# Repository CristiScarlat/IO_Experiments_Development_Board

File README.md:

IO_Experiments is a developer kit on a single board. The developer can connect any uC board including Arduino , Nucleo , RasperryPi to any of the devices on this board.

The board contains:
1. LCD 16x2 alphanumeric;
2. 8xleds driven by ULN2803;
3. 8xpush buttons;
4. 8xPots;
5. 7 segment display driven with cd4511;
6. 1x led matrix display driven by a MAX7219
7. 1xConnection made for Aurel 433MHz transiver;
8. 1xRTC PCF8563 I2C;
9. 3xIO Expanders MCP23017 I2C;
10. 1xEEPROM AT24CP I2C;
11. 1xFLASH MEM 25VF512A SPI ;
12. 1xDC Motor Drive L298;
13. 8xToggle Switches;
14. 1xRotary Encoder;
15. 1xJoystick;
16. 1xPiezzo Buzzer;
17. 1xLight Sensor;
18. 1xTemperature Sensor TMP36;
19 1xIR sensor 38KHz TSOP3483;
10. 1xDAC 12bit MCP4921 SPI ;
11. 1xADC 12bit MCP3201 SPI;
12. 8xRelays driven by ULN2803;

The boards has a 5V 3A power regulator and 3.3V 800mA power regulator.

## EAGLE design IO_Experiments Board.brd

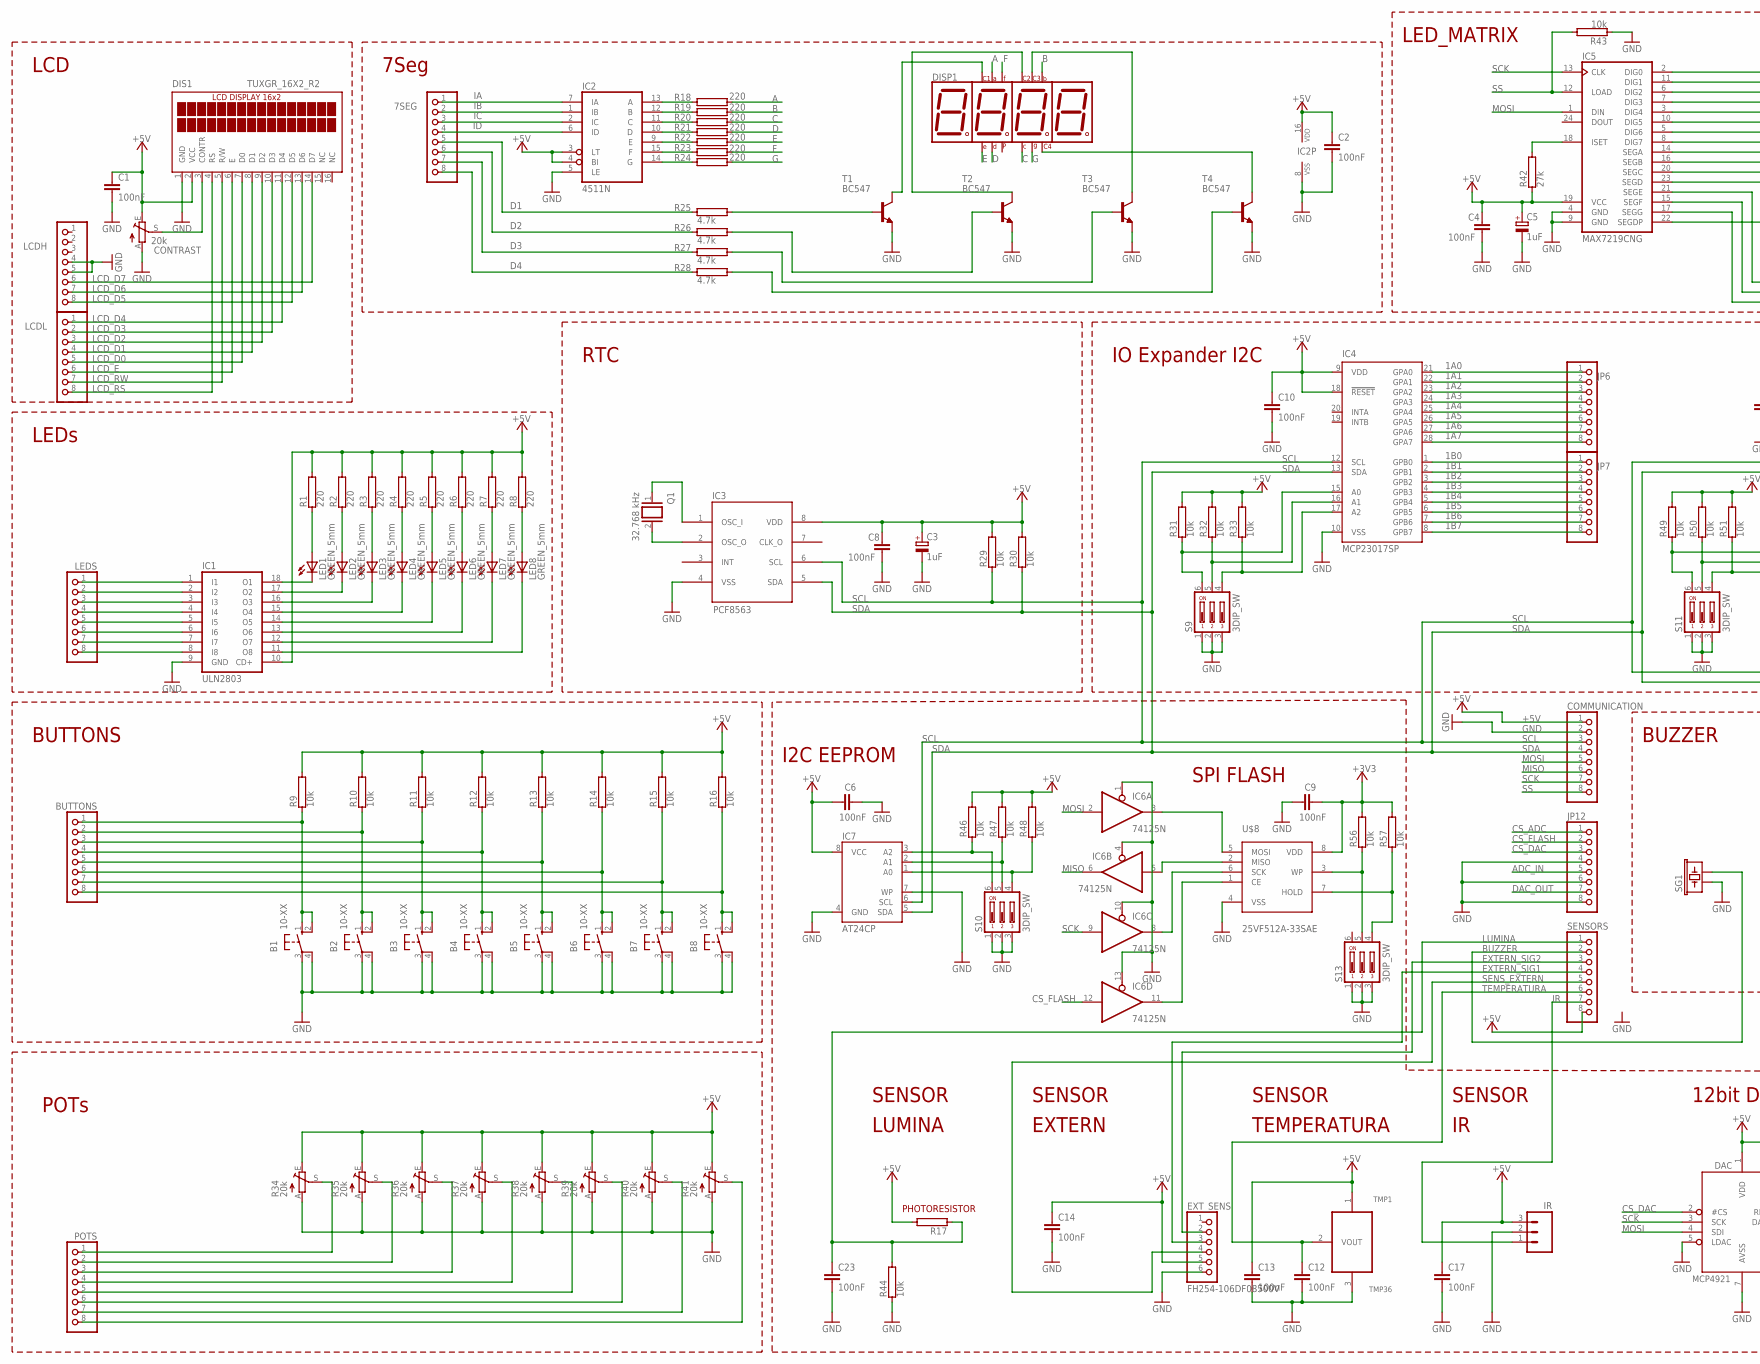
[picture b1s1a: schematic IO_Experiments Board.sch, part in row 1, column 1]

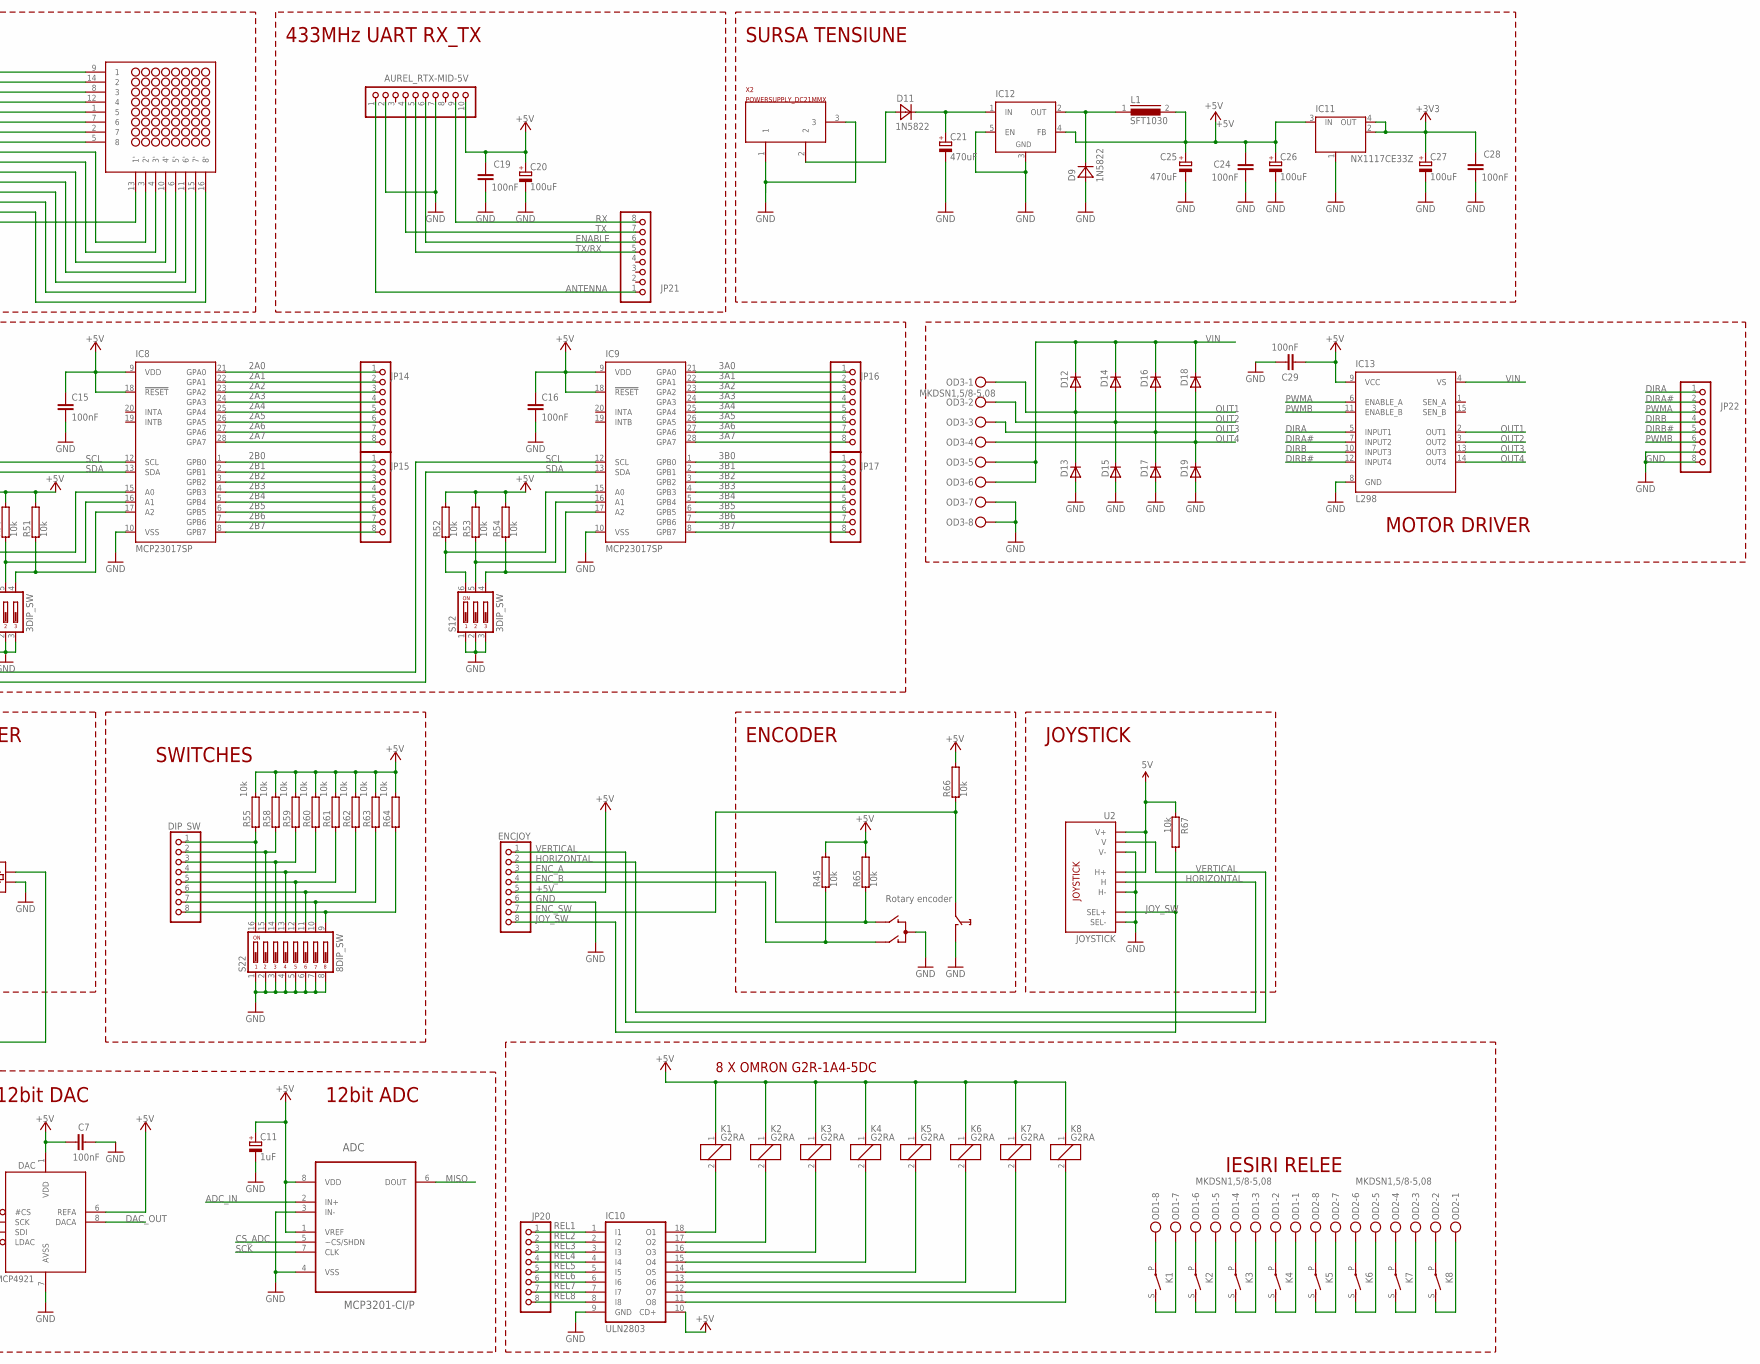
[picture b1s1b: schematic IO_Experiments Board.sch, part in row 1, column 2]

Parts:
7SEG: FH254-108DF08500V; 1X08
ADC: MCP3201-CI/P; DIL08
AUREL_RTX-MID-5V: FH254-110DF08500V; 1X10
B1, B2, B3, B4, B5, B6, B7, B8: 10-XX; B3F-10XX
BUTTONS: FH254-108DF08500V; 1X08
C1, C2, C4, C6, C7, C8, C9, C10, C12, C13, C14, C15, C16, C17, C19, C23, C24, C28, C29: 100nF; C5B2.5
C3, C5: 1uF; E2,5-6
C11: 1uF; E2,5-5
C20, C26, C27: 100uF; E2,5-6
C21, C25: 470uF; E5-10,5
COMMUNICATION: FH254-108DF08500V; 1X08
CONTRAST: 20k; CA6V
D9, D11: 1N5822; DO201-15
D12, D13, D14, D15, D16, D17, D18, D19: MBRA140; DO201-15
DAC: MCP4921; DIL08
DIP_SW: FH254-108DF08500V; 1X08
DIS1: TUXGR_16X2_R2
DISP1: LFD039AUE
ENCJOY: FH254-108DF08500V; 1X08
EXT_SENS: FH254-106DF08500V; 1X06
IC1, IC10: ULN2803; DIL18
IC2: 4511N; DIL16
IC3: PCF8563P; DIL08
IC4, IC8, IC9: MCP23017SP; DIL28-3
IC5: MAX7219CNG; DIL24-3
IC6: 74125N; DIL14
IC7: AT24CP; DIL08
IC11: NX1117CE33Z; SOT223
IC12: LM2596TV; TO220-51
IC13: L298; MULTIWATT-15
IR: M03LONGPADS; 1X03_LONGPADS
JP6, JP7, JP12, JP14, JP15, JP16, JP17, JP20, JP21, JP22: FH254-108DF08500V; 1X08
K1, K2, K3, K4, K5, K6, K7, K8: G2RA
L1: SFT1030
LCDH: FH254-108DF08500V; 1X08
LCDL: FH254-108DF08500V; 1X08
LED1, LED2, LED3, LED4, LED5, LED6, LED7, LED8: GREEN_5mm; LED5MM
LEDS: FH254-108DF08500V; 1X08
OD1, OD2, OD3: MKDSN1,5/8-5,08
POTS: FH254-108DF08500V; 1X08
Q1: 32.768 kHz; QS
R1, R2, R3, R4, R5, R6, R7, R8, R18, R19, R20, R21, R22, R23, R24: 220; RS1/8
R9, R10, R11, R12, R13, R14, R15, R16, R29, R30, R31, R32, R33, R43, R44, R45, R46, R47, R48, R49, R50, R51, R52, R53, R54, R55, R56, R57, R58, R59, R60, R61, R62, R63, R64, R65, R66, R67: 10k; RS1/8
R17: RRS1/8; RS1/8
R25, R26, R27, R28: 4.7k; RS1/8
R34, R35, R36, R37, R38, R39, R40, R41: 20k; CA6V
R42: 27k; RS1/8
S9, S10, S11, S12, S13: 3DIP_SW; DS-03
S22: 8DIP_SW; DS-08
SENSORS: FH254-108DF08500V; 1X08
SG1: 0550_PKM13EPYH4002-B0; BUZZER-12MM-NS-P5MM
SW1: EC12E_SW; ALPS_EC12E_SW
T1, T2, T3, T4: BC547; TO92
TMP1: TMP36; BC-TO92
U2: JOYSTICK
U$5: LMD12088AUE-101A; NFM-12881BG-11
U$8: 25VF512A-33SAE; SOIC-8
X2: POWERSUPPLY_DC21MMX; POWERSUPPLY_DC-21MM

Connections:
1A0: IC4.21 (GPA0), JP6.1
1A1: IC4.22 (GPA1), JP6.2
1A2: IC4.23 (GPA2), JP6.3
1A3: IC4.24 (GPA3), JP6.4
1A4: IC4.25 (GPA4), JP6.5
1A5: IC4.26 (GPA5), JP6.6
1A6: IC4.27 (GPA6), JP6.7
1A7: IC4.28 (GPA7), JP6.8
1B0: IC4.1 (GPB0), JP7.1
1B1: IC4.2 (GPB1), JP7.2
1B2: IC4.3 (GPB2), JP7.3
1B3: IC4.4 (GPB3), JP7.4
1B4: IC4.5 (GPB4), JP7.5
1B5: IC4.6 (GPB5), JP7.6
1B6: IC4.7 (GPB6), JP7.7
1B7: IC4.8 (GPB7), JP7.8
2A0: IC8.21 (GPA0), JP14.1
2A1: IC8.22 (GPA1), JP14.2
2A2: IC8.23 (GPA2), JP14.3
2A3: IC8.24 (GPA3), JP14.4
2A4: IC8.25 (GPA4), JP14.5
2A5: IC8.26 (GPA5), JP14.6
2A6: IC8.27 (GPA6), JP14.7
2A7: IC8.28 (GPA7), JP14.8
2B0: IC8.1 (GPB0), JP15.1
2B1: IC8.2 (GPB1), JP15.2
2B2: IC8.3 (GPB2), JP15.3
2B3: IC8.4 (GPB3), JP15.4
2B4: IC8.5 (GPB4), JP15.5
2B5: IC8.6 (GPB5), JP15.6
2B6: IC8.7 (GPB6), JP15.7
2B7: IC8.8 (GPB7), JP15.8
3A0: IC9.21 (GPA0), JP16.1
3A1: IC9.22 (GPA1), JP16.2
3A2: IC9.23 (GPA2), JP16.3
3A3: IC9.24 (GPA3), JP16.4
3A4: IC9.25 (GPA4), JP16.5
3A5: IC9.26 (GPA5), JP16.6
3A6: IC9.27 (GPA6), JP16.7
3A7: IC9.28 (GPA7), JP16.8
3B0: IC9.1 (GPB0), JP17.1
3B1: IC9.2 (GPB1), JP17.2
3B2: IC9.3 (GPB2), JP17.3
3B3: IC9.4 (GPB3), JP17.4
3B4: IC9.5 (GPB4), JP17.5
3B5: IC9.6 (GPB5), JP17.6
3B6: IC9.7 (GPB6), JP17.7
3B7: IC9.8 (GPB7), JP17.8
+3V3: C9.2, C27.+, C28.1, IC11.2 (OUT), IC11.4 (OUT), R56.2, R57.2, U$8.8 (VDD)
+5V: ADC.1 (VREF), ADC.8 (VDD), AUREL_RTX-MID-5V.10, C1.1, C2.1, C3.+, C4.1, C5.+, C6.1, C7.1, C8.1, C10.1, C11.+, C13.1, C14.1, C15.1, C16.1, C17.1, C19.1, C20.+, C24.1, C25.+, C26.+, C29.1, COMMUNICATION.1, CONTRAST.E, DAC.1 (VDD), DAC.6 (REFA), DIS1.2 (VCC), ENCJOY.5, EXT_SENS.5, IC1.10 (CD+), IC2.3 (LT), IC2.4 (BI), IC2.16 (VDD), IC3.8 (VDD), IC4.9 (VDD), IC4.18 (!RESET), IC5.19 (VCC), IC7.8 (VCC), IC8.9 (VDD), IC8.18 (!RESET), IC9.9 (VDD), IC9.18 (!RESET), IC10.10 (CD+), IC11.3 (IN), IC12.4 (FB), IC13.9 (VCC), IR.3, K1.1, K2.1, K3.1, K4.1, K5.1, K6.1, K7.1, K8.1, L1.2, R1.2, R2.2, R3.2, R4.2, R5.2, R6.2, R7.2, R8.2, R9.2, R10.2, R11.2, R12.2, R13.2, R14.2, R15.2, R16.2, R17.2, R29.2, R30.2, R31.2, R32.2, R33.2, R34.E, R35.E, R36.E, R37.E, R38.E, R39.E, R40.E, R41.E, R42.1, R45.2, R46.2, R47.2, R48.2, R49.2, R50.2, R51.2, R52.2, R53.2, R54.2, R55.2, R58.2, R59.2, R60.2, R61.2, R62.2, R63.2, R64.2, R65.2, R66.2, R67.1, SENSORS.8, TMP1.1 (+VS), U2.H1 (H+), U2.V1 (V+)
A: DISP1.11 (A), R18.2
ADC_IN: ADC.2 (IN+), JP12.5
ANTENNA: AUREL_RTX-MID-5V.1, JP21.1
B: DISP1.7 (B), R19.2
BUZZER: SENSORS.2, SG1.- (2)
C: DISP1.4 (C), R20.2
CONTRAST: CONTRAST.S, DIS1.3 (CONTR)
CS_ADC: ADC.5 (~CS/SHDN), JP12.1
CS_DAC: DAC.2 (#CS), JP12.3
CS_FLASH: IC6.12 (I), JP12.2
D: DISP1.2 (D), R21.2
D1: 7SEG.5, R25.1
D2: 7SEG.6, R26.1
D3: 7SEG.7, R27.1
D4: 7SEG.8, R28.1
DAC_OUT: DAC.8 (DACA), JP12.7
DIRA: IC13.5 (INPUT1), JP22.1
DIRA#: IC13.7 (INPUT2), JP22.2
DIRB: IC13.10 (INPUT3), JP22.4
DIRB#: IC13.12 (INPUT4), JP22.5
E: DISP1.1 (E), R22.2
ENABLE: AUREL_RTX-MID-5V.6, JP21.6
ENC_A: ENCJOY.3, R65.1, SW1.B
ENC_B: ENCJOY.4, R45.1, SW1.A
ENC_SW: ENCJOY.7, R66.1, SW1.E (2)
EXTERN_SIG1: EXT_SENS.3, SENSORS.4
EXTERN_SIG2: EXT_SENS.2, SENSORS.3
F: DISP1.10 (F), R23.2
G: DISP1.5 (G), R24.2
GND: ADC.3 (IN-), ADC.4 (VSS), AUREL_RTX-MID-5V.2, AUREL_RTX-MID-5V.7, B1.3, B1.4 (P1), B2.3, B2.4 (P1), B3.3, B3.4 (P1), B4.3, B4.4 (P1), B5.3, B5.4 (P1), B6.3, B6.4 (P1), B7.3, B7.4 (P1), B8.3, B8.4 (P1), C1.2, C2.2, C3.-, C4.2, C5.-, C6.2, C7.2, C8.2, C9.1, C10.2, C11.-, C12.2, C13.2, C14.2, C15.2, C16.2, C17.2, C19.2, C20.-, C21.-, C23.2, C24.2, C25.-, C26.-, C27.-, C28.2, C29.2, COMMUNICATION.2, CONTRAST.A, D9.A, D13.A, D15.A, D17.A, D19.A, DAC.5 (LDAC), DAC.7 (AVSS), DIS1.1 (GND), ENCJOY.6, EXT_SENS.6, IC1.9 (GND), IC2.5 (LE), IC2.8 (VSS), IC3.4 (VSS), IC4.10 (VSS), IC5.4 (GND), IC5.9 (GND), IC6.1 (OE), IC6.4 (OE), IC6.7 (GND), IC6.10 (OE), IC6.13 (OE), IC7.4 (GND), IC7.7 (WP), IC8.10 (VSS), IC9.10 (VSS), IC10.9 (GND), IC11.1 (GND/ADJ), IC12.3 (GND), IC12.5 (EN), IC13.8 (GND), IR.2, JP12.4, JP12.6, JP12.8, JP22.7, JP22.8, LCDH.4, LCDH.5, OD3.7, OD3.8, R34.A, R35.A, R36.A, R37.A, R38.A, R39.A, R40.A, R41.A, R43.1, R44.1, S9.1, S9.2, S9.3, S10.1, S10.2, S10.3, S11.1, S11.2, S11.3, S12.1, S12.2, S12.3, S13.1, S13.2, S13.3, S22.1, S22.2, S22.3, S22.4, S22.5, S22.6, S22.7, S22.8, SG1.+ (1), SW1.C, SW1.D (1), T1.1 (E), T2.1 (E), T3.1 (E), T4.1 (E), TMP1.3 (GND), U2.B2A (SEL-), U2.H3 (H-), U2.V3 (V-), U$8.4 (VSS), X2.1, X2.3
HORIZONTAL: ENCJOY.2, U2.H2 (H)
IA: 7SEG.1, IC2.7 (IA)
IB: 7SEG.2, IC2.1 (IB)
IC: 7SEG.3, IC2.2 (IC)
ID: 7SEG.4, IC2.6 (ID)
IR: IR.1, SENSORS.7
JOY_SW: ENCJOY.8, R67.2, U2.B1A (SEL+)
LCD_D0: DIS1.7 (D0), LCDL.5
LCD_D1: DIS1.8 (D1), LCDL.4
LCD_D2: DIS1.9 (D2), LCDL.3
LCD_D3: DIS1.10 (D3), LCDL.2
LCD_D4: DIS1.11 (D4), LCDL.1
LCD_D5: DIS1.12 (D5), LCDH.8
LCD_D6: DIS1.13 (D6), LCDH.7
LCD_D7: DIS1.14 (D7), LCDH.6
LCD_E: DIS1.6 (E), LCDL.6
LCD_RS: DIS1.4 (RS), LCDL.8
LCD_RW: DIS1.5 (R/W), LCDL.7
LUMINA: C23.1, R17.1, R44.2, SENSORS.1
MISO: ADC.6 (DOUT), COMMUNICATION.6, IC6.6 (O)
MOSI: COMMUNICATION.5, DAC.4 (SDI), IC5.1 (DIN), IC6.2 (I)
unnamed: IC1.1 (I1), LEDS.1
unnamed: IC1.2 (I2), LEDS.2
unnamed: IC1.3 (I3), LEDS.3
unnamed: IC1.4 (I4), LEDS.4
unnamed: IC1.5 (I5), LEDS.5
unnamed: IC1.6 (I6), LEDS.6
unnamed: IC1.7 (I7), LEDS.7
unnamed: IC1.8 (I8), LEDS.8
unnamed: IC1.18 (O1), LED1.K (C)
unnamed: IC1.17 (O2), LED2.K (C)
unnamed: IC1.16 (O3), LED3.K (C)
unnamed: IC1.15 (O4), LED4.K (C)
unnamed: IC1.14 (O5), LED5.K (C)
unnamed: IC1.13 (O6), LED6.K (C)
unnamed: IC1.12 (O7), LED7.K (C)
unnamed: IC1.11 (O8), LED8.K (C)
unnamed: LED1.A, R1.1
unnamed: LED2.A, R2.1
unnamed: LED3.A, R3.1
unnamed: LED4.A, R4.1
unnamed: LED5.A, R5.1
unnamed: LED6.A, R6.1
unnamed: LED7.A, R7.1
unnamed: LED8.A, R8.1
unnamed: B1.1 (S), B1.2 (S1), BUTTONS.1, R9.1
unnamed: B2.1 (S), B2.2 (S1), BUTTONS.2, R10.1
unnamed: B3.1 (S), B3.2 (S1), BUTTONS.3, R11.1
unnamed: B4.1 (S), B4.2 (S1), BUTTONS.4, R12.1
unnamed: B5.1 (S), B5.2 (S1), BUTTONS.5, R13.1
unnamed: B6.1 (S), B6.2 (S1), BUTTONS.6, R14.1
unnamed: B7.1 (S), B7.2 (S1), BUTTONS.7, R15.1
unnamed: B8.1 (S), B8.2 (S1), BUTTONS.8, R16.1
unnamed: IC2.13 (A), R18.1
unnamed: IC2.12 (B), R19.1
unnamed: IC2.11 (C), R20.1
unnamed: IC2.10 (D), R21.1
unnamed: IC2.9 (E), R22.1
unnamed: IC2.15 (F), R23.1
unnamed: IC2.14 (G), R24.1
unnamed: DISP1.12 (CC1), T1.3 (C)
unnamed: DISP1.9 (CC2), T2.3 (C)
unnamed: DISP1.8 (CC3), T3.3 (C)
unnamed: DISP1.6 (CC4), T4.3 (C)
unnamed: R26.2, T2.2 (B)
unnamed: R27.2, T3.2 (B)
unnamed: R28.2, T4.2 (B)
unnamed: R25.2, T1.2 (B)
unnamed: IC3.1 (OSC_I), Q1.1
unnamed: IC3.2 (OSC_O), Q1.2
unnamed: IC5.2 (DIG0), U$5.9 (1)
unnamed: IC5.11 (DIG1), U$5.14 (2)
unnamed: POTS.1, R34.S
unnamed: POTS.2, R35.S
unnamed: IC4.15 (A0), R31.1, S9.6
unnamed: IC4.16 (A1), R32.1, S9.5
unnamed: IC4.17 (A2), R33.1, S9.4
unnamed: POTS.3, R36.S
unnamed: POTS.4, R37.S
unnamed: POTS.5, R38.S
unnamed: POTS.6, R39.S
unnamed: POTS.7, R40.S
unnamed: POTS.8, R41.S
unnamed: K1.P, OD1.8
unnamed: IC5.6 (DIG2), U$5.8 (3)
unnamed: IC5.7 (DIG3), U$5.12 (4)
unnamed: IC5.3 (DIG4), U$5.1 (5)
unnamed: IC5.10 (DIG5), U$5.7 (6)
unnamed: IC5.5 (DIG6), U$5.2 (7)
unnamed: IC5.8 (DIG7), U$5.5 (8)
unnamed: IC5.22 (SEGDP), U$5.13 (1')
unnamed: IC5.17 (SEGG), U$5.16 (8')
unnamed: IC5.14 (SEGA), U$5.3 (2')
unnamed: IC5.16 (SEGB), U$5.4 (3')
unnamed: IC5.20 (SEGC), U$5.10 (4')
unnamed: IC5.23 (SEGD), U$5.6 (5')
unnamed: IC5.21 (SEGE), U$5.11 (6')
unnamed: IC5.15 (SEGF), U$5.15 (7')
unnamed: IC5.18 (ISET), R42.2
unnamed: IC7.1 (A0), R48.1, S10.4
unnamed: IC7.2 (A1), R47.1, S10.5
unnamed: IC7.3 (A2), R46.1, S10.6
unnamed: IC8.15 (A0), R49.1, S11.6
unnamed: IC8.16 (A1), R50.1, S11.5
unnamed: IC8.17 (A2), R51.1, S11.4
unnamed: IC9.15 (A0), R52.1, S12.6
unnamed: IC9.16 (A1), R53.1, S12.5
unnamed: IC9.17 (A2), R54.1, S12.4
unnamed: K1.S, OD1.7
unnamed: K2.P, OD1.6
unnamed: K2.S, OD1.5
unnamed: K3.P, OD1.4
unnamed: K3.S, OD1.3
unnamed: K4.P, OD1.2
unnamed: K4.S, OD1.1
unnamed: K5.P, OD2.8
unnamed: IC10.18 (O1), K1.2
unnamed: IC10.17 (O2), K2.2
unnamed: IC10.16 (O3), K3.2
unnamed: IC10.15 (O4), K4.2
unnamed: IC10.14 (O5), K5.2
unnamed: IC10.13 (O6), K6.2
unnamed: IC10.12 (O7), K7.2
unnamed: IC10.11 (O8), K8.2
unnamed: K5.S, OD2.7
unnamed: K6.P, OD2.6
unnamed: K6.S, OD2.5
unnamed: K7.P, OD2.4
unnamed: K7.S, OD2.3
unnamed: K8.P, OD2.2
unnamed: K8.S, OD2.1
unnamed: IC6.5 (I), U$8.2 (MISO)
unnamed: IC6.3 (O), U$8.5 (MOSI)
unnamed: IC6.8 (O), U$8.6 (SCK)
unnamed: C21.+, D11.C, IC12.1 (IN)
unnamed: IC6.11 (O), U$8.1 (CE)
unnamed: R56.1, S13.5, U$8.3 (WP)
unnamed: R57.1, S13.4, U$8.7 (HOLD)
unnamed: D9.C, IC12.2 (OUT), L1.1
unnamed: D11.A, X2.2
unnamed: DIP_SW.1, R55.1, S22.16
unnamed: DIP_SW.2, R58.1, S22.15
unnamed: DIP_SW.3, R59.1, S22.14
unnamed: DIP_SW.4, R60.1, S22.13
unnamed: DIP_SW.5, R61.1, S22.12
unnamed: DIP_SW.6, R62.1, S22.11
unnamed: DIP_SW.7, R63.1, S22.10
unnamed: DIP_SW.8, R64.1, S22.9
OUT1: D12.A, D13.C, IC13.2 (OUT1), OD3.1
OUT2: D14.A, D15.C, IC13.3 (OUT2), OD3.2
OUT3: D16.A, D17.C, IC13.13 (OUT3), OD3.3
OUT4: D18.A, D19.C, IC13.14 (OUT4), OD3.4
PWMA: IC13.6 (ENABLE_A), JP22.3
PWMB: IC13.11 (ENABLE_B), JP22.6
REL1: IC10.1 (I1), JP20.1
REL2: IC10.2 (I2), JP20.2
REL3: IC10.3 (I3), JP20.3
REL4: IC10.4 (I4), JP20.4
REL5: IC10.5 (I5), JP20.5
REL6: IC10.6 (I6), JP20.6
REL7: IC10.7 (I7), JP20.7
REL8: IC10.8 (I8), JP20.8
RX: AUREL_RTX-MID-5V.9, JP21.8
SCK: ADC.7 (CLK), COMMUNICATION.7, DAC.3 (SCK), IC5.13 (CLK), IC6.9 (I)
SCL: COMMUNICATION.3, IC3.6 (SCL), IC4.12 (SCL), IC7.6 (SCL), IC8.12 (SCL), IC9.12 (SCL), R29.1
SDA: COMMUNICATION.4, IC3.5 (SDA), IC4.13 (SDA), IC7.5 (SDA), IC8.13 (SDA), IC9.13 (SDA), R30.1
SENS_EXTERN: EXT_SENS.4, SENSORS.5
SS: COMMUNICATION.8, IC5.12 (LOAD), R43.2
TEMPERATURA: C12.1, SENSORS.6, TMP1.2 (VOUT)
TX: AUREL_RTX-MID-5V.4, JP21.7
TX/RX: AUREL_RTX-MID-5V.5, JP21.5
VCC: IC6.14 (VCC)
VERTICAL: ENCJOY.1, U2.V2 (V)
VIN: D12.C, D14.C, D16.C, D18.C, IC13.4 (VS), OD3.5, OD3.6

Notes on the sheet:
RTC
LCD
LEDs
BUTTONS
7Seg
IO Expander I2C
POTs
LED_MATRIX
PHOTORESISTOR
SENSOR
LUMINA
EXTERN
TEMPERATURA
12bit DAC
I2C EEPROM
SPI FLASH
12bit ADC
JOYSTICK
BUZZER
8 X OMRON G2R-1A4-5DC
IESIRI RELEE
433MHz UART RX_TX
SURSA TENSIUNE
MOTOR DRIVER
SWITCHES
Rotary encoder
ENCODER

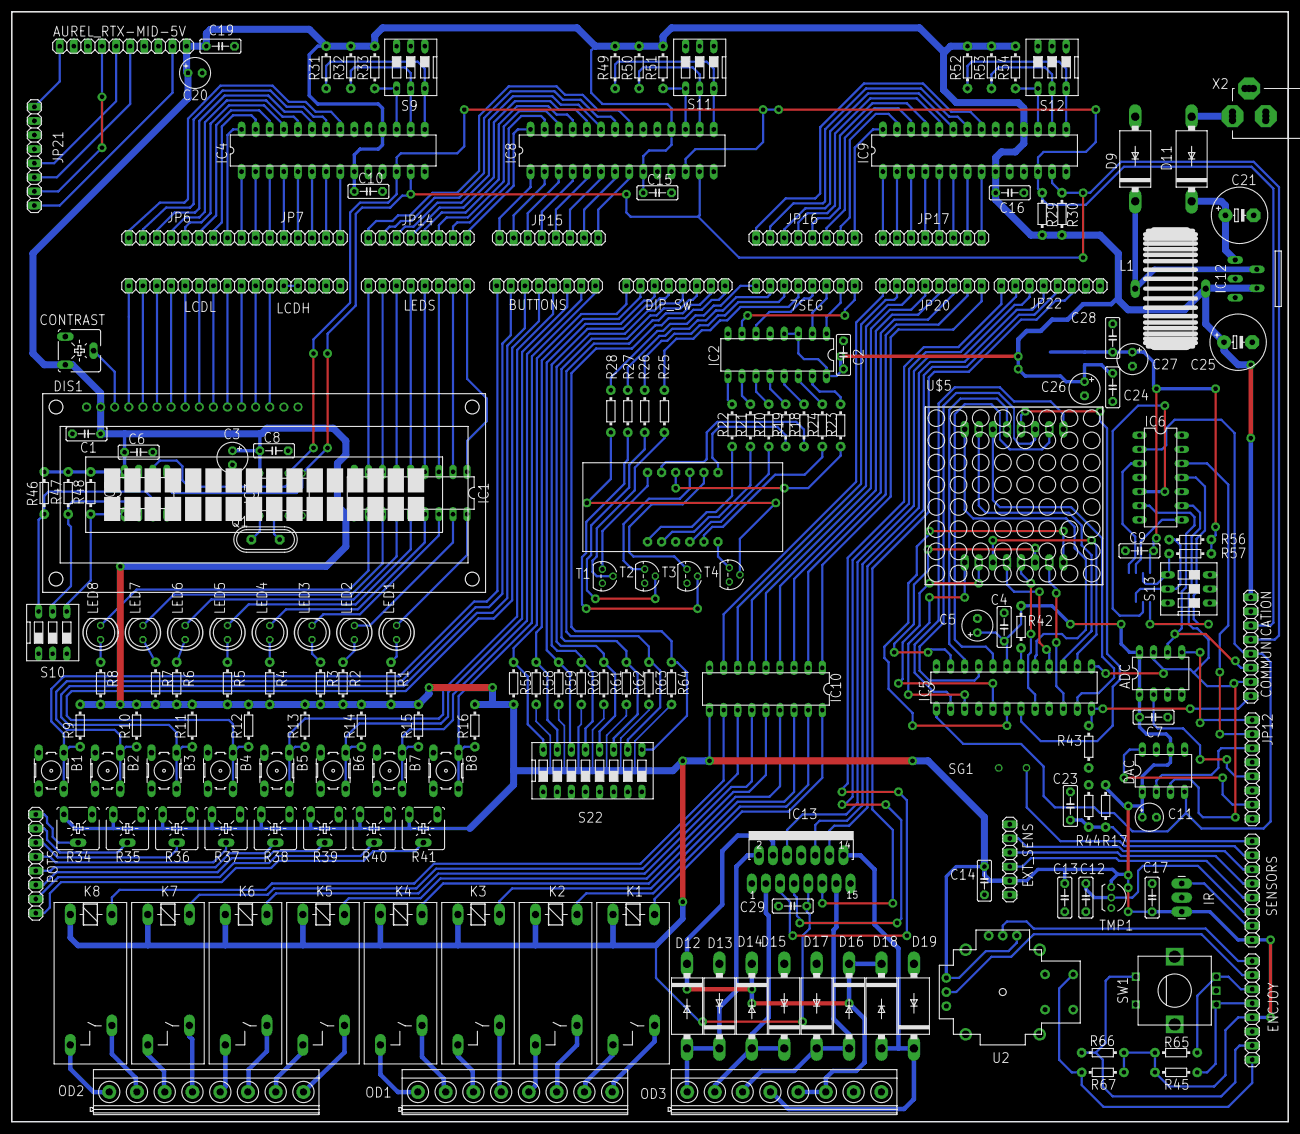
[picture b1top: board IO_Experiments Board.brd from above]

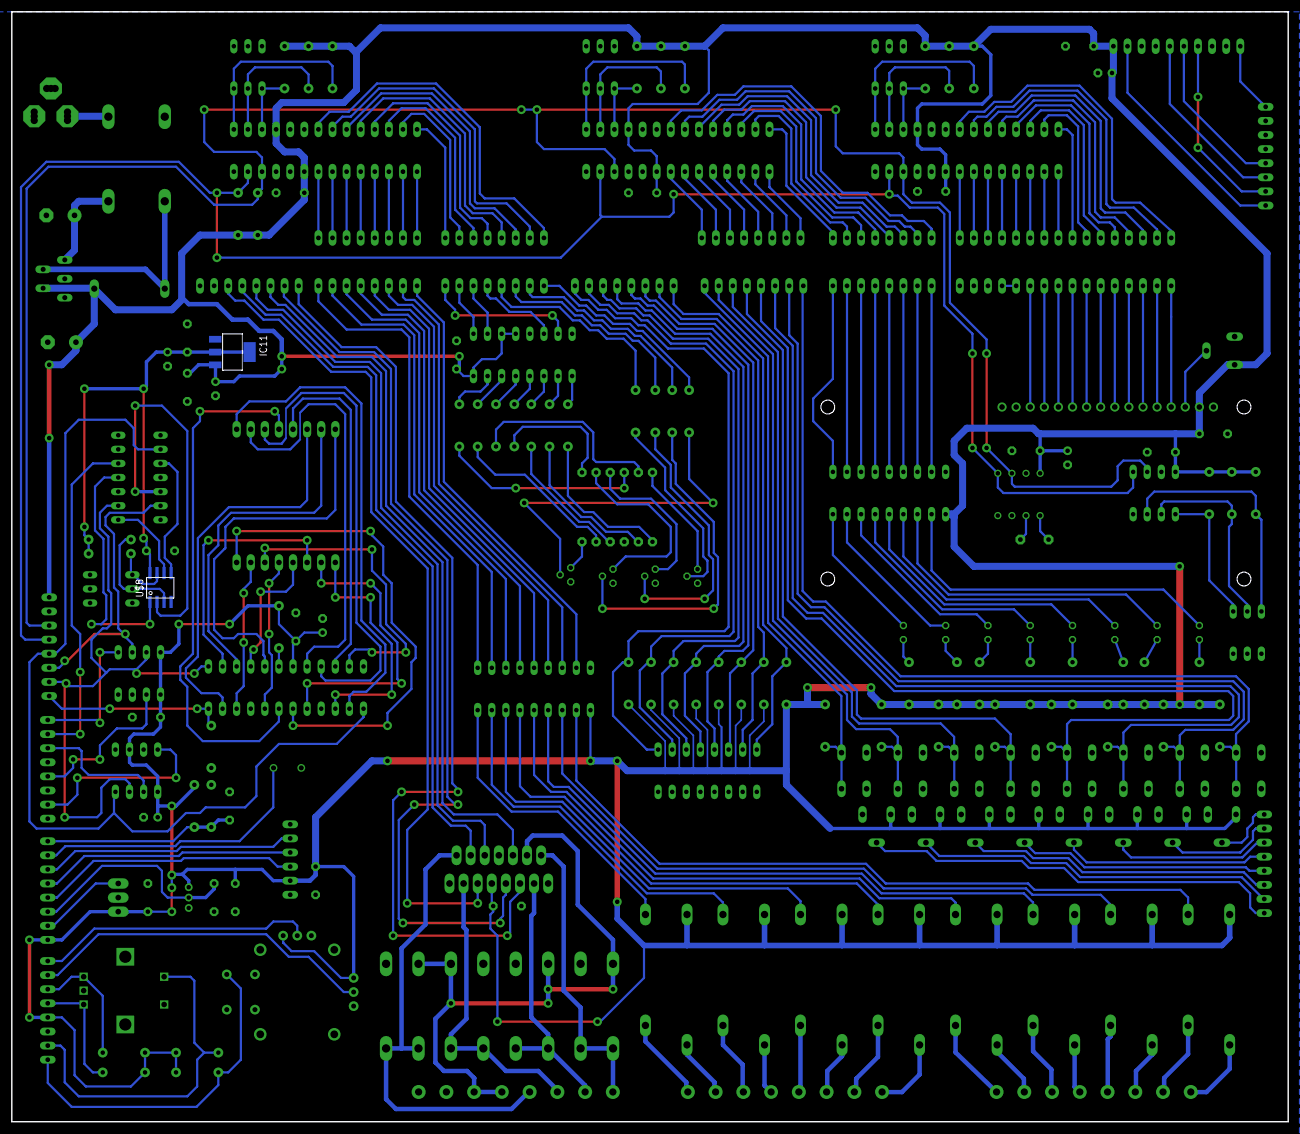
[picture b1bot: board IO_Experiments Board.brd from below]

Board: 2 copper layers, 230.0 x 200.0 mm, 191 parts (2 on the bottom side), 253 nets.

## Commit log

2018-09-09 pushed all the working files
2019-10-19 added signal names on connectors on the board , layer 51

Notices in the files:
parts and their libraries:
eagle-library-edeca.net-v5: This is v1 and is licensed under the Creative Commons (Attribution-Non-Commercial-Share Alike 2.0 UK)
